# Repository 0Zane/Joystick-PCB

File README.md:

# JOYSTICK PCB

The Joystick PCB is a prototype to facilitate the usage of joysticks along with classic devboards.

The PCB contains a 01*05 socket pin connector folliwing this order (up to down):
-VCC
-X axis
-Y axis
-SW_OUT
-GND

A pull-up resistor is used close to the push switch with a value of 10Kohms.

This project is a beginner project so i don't recommend using the V1.0 since others professional PCBs are existing. (see *CONTEXT*)

# CONTEXT
This project is my first project desinging a custom PCB to complete a task.

First of all i got a joystick by breaking an old controller ( joystick RSF ) , and i wanted to use it with my ESP32.
The problem is that there are too many pins on this joystick , and i did not want to do another perfboard horrible project so i decided to learn how to do a real PCB using KiCad, a free PCB design suite.

After learning the basics i did multiple versions of the schematic and ended up finding some open source symbols and footprints for the joystick itself because KiCad is not providing symbol and footprint for this joystick .

Then i completed the first version of the PCB using [this footprint for the joystick](https://github.com/redsaber42/GameController/blob/main/Joystick.kicad_mod)

# USED SOFTWARE

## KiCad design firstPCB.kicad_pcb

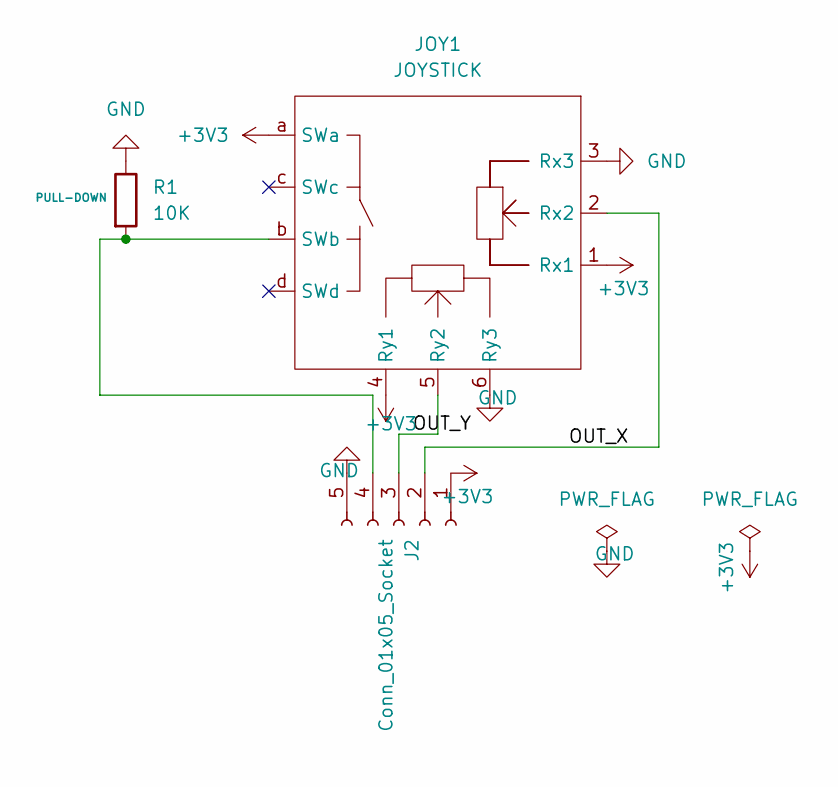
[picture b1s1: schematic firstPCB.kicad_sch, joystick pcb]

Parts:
J2: Conn_01x05_Socket; PinSocket_1x05_P2.00mm_Vertical
JOY1: JOYSTICK; Joystick
R1: 10K; R_0805_2012Metric_Pad1.20x1.40mm_HandSolder

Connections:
+3V3: J2.1, JOY1.1 (Rx1), JOY1.4 (Ry1), JOY1.a (SWa)
/OUT_X: J2.2, JOY1.2 (Rx2)
/OUT_Y: J2.3, JOY1.5 (Ry2)
GND: J2.5, JOY1.3 (Rx3), JOY1.6 (Ry3), R1.1
unnamed: J2.4, JOY1.b (SWb), R1.2

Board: 2 copper layers, 3 parts (0 on the bottom side), 5 nets, no tracks yet.

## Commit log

2025-12-05 Update README.md
    Making the first explanations of the project
2025-12-05 Add files via upload
    Adding the schematic file
2025-12-13 Add files via upload
    Adding first version of the PCB , not routed yet but correctly assigned with the schematic and the footprints
2025-12-13 Add files via upload
    New version of schematic more adapted to the PCB & footprints
2025-12-31 Adding the PCB file
    Routing is done
2026-01-01 Adding visual assets and updating README.md
2026-01-01 Adding schematic image
2026-01-01 Update README with images and project details
2026-01-01 Fix heading formatting in README.md
    Updated headings in README.md for consistency.
2026-01-01 Fix badge syntax in README.md
